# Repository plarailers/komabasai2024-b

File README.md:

# 第75回駒場祭（プランB）

開催日：2024年11月22日（金）～24日（日）

## 内容

【自動運転】
- train
  - 列車に書き込むコード
- master_controller
  - マスコンに書き込むコード
- wire_pole
  - 架線柱に書き込むコード
- point_switching
  - ポイントに書き込むコード
- ptcs
  - PC側の列車制御システム

【その他】
- experimental
  - 実験的なコードを置くところ
- rotary_encoder
  - ロータリーエンコーダの動作確認
- HiFreq_ADC
  - モータ電流ノイズを用いたIPSの実験

## インストール

```sh
git clone https://github.com/plarailers/komabasai2024-b.git
```

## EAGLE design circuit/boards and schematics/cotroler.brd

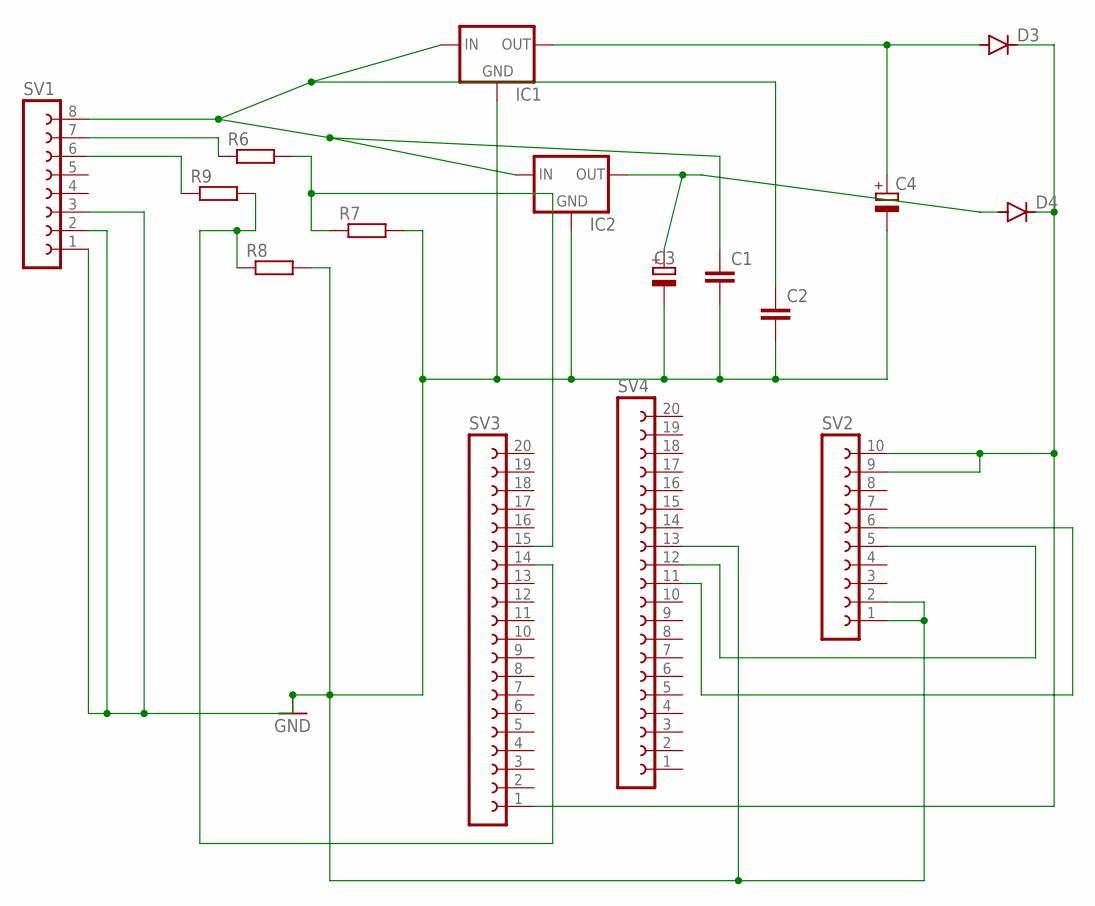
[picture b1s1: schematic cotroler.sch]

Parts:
C1, C2: C-EU025-024X044; C025-024X044
C3, C4: CPOL-EUE2.5-5; E2,5-5
D3, D4: DIODE-D-10; D-10
IC1, IC2: 78XXS
R6, R7, R8, R9: R-EU_0207/10; 0207/10
SV1: FE08-1; FE08
SV2: FE10-1; FE10
SV3, SV4: FE20-1; FE20

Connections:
GND: C1.2, C2.2, C3.-, C4.-, IC1.GND, IC2.GND, R7.2, R8.2, SV1.1, SV1.2, SV1.3, SV2.1, SV2.2, SV4.13
unnamed: R6.1, SV1.7
unnamed: SV2.5, SV4.12
unnamed: C1.1, C2.1, IC1.IN, IC2.IN, SV1.8
unnamed: R6.2, R7.1, SV3.15
unnamed: R9.1, SV1.6
unnamed: R8.1, R9.2, SV3.14
unnamed: C3.+, D4.A, IC2.OUT
unnamed: C4.+, D3.A, IC1.OUT
unnamed: SV2.6, SV4.11
unnamed: D3.C, D4.C, SV2.9, SV2.10, SV3.1

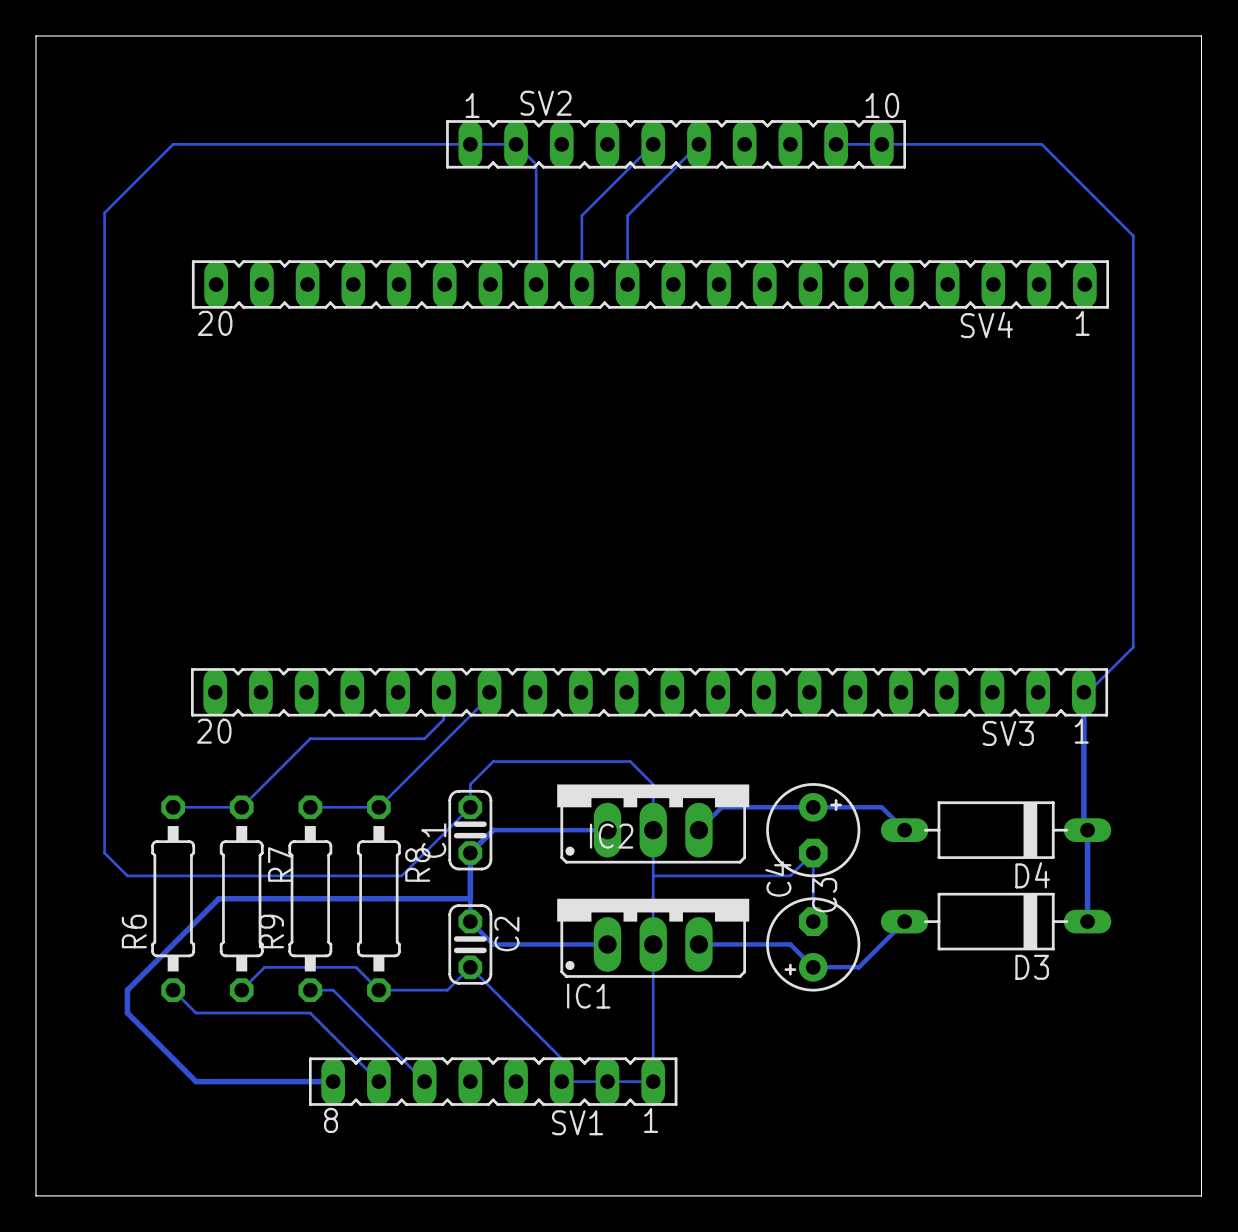
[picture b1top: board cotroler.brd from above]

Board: 2 copper layers, 64.8 x 64.4 mm, 16 parts (0 on the bottom side), 11 nets.

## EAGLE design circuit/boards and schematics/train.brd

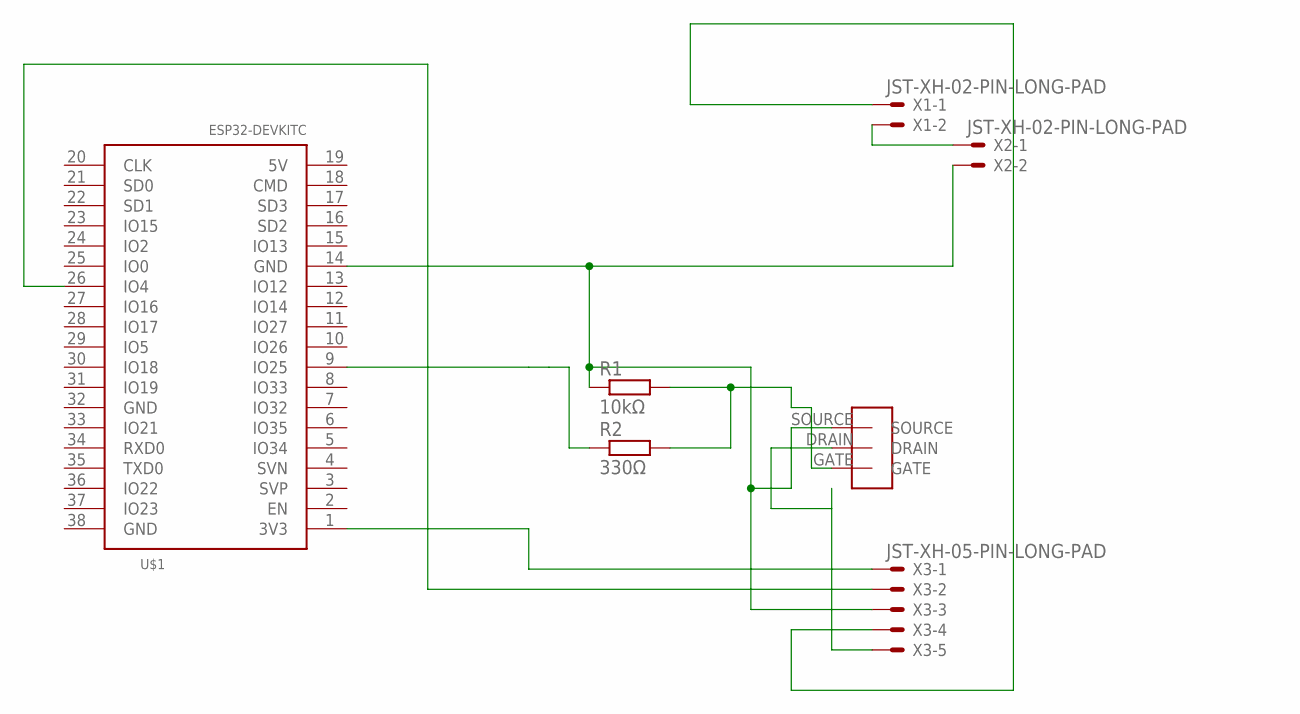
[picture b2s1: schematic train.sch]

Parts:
FET1: FET
R1: 10kΩ; 0207/10
R2: 330Ω; 0207/10
U$1: ESP32DEVKITC; ESP32-DEVKITC
X1, X2: JST-XH-02-PIN-LONG-PAD; JST-XH-02-PACKAGE-LONG-PAD
X3: JST-XH-05-PIN-LONG-PAD; JST-XH-05-PACKAGE-LONG-PAD

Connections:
unnamed: X1.1, X3.4
unnamed: FET1.SOURCE, R1.1, U$1.14 (GND), X2.2, X3.3
unnamed: FET1.GATE, R1.2, R2.2
unnamed: R2.1, U$1.9 (IO25)
unnamed: X1.2, X2.1
unnamed: U$1.1 (3V3), X3.1
unnamed: U$1.26 (IO4), X3.2
unnamed: FET1.DRAIN, X3.5

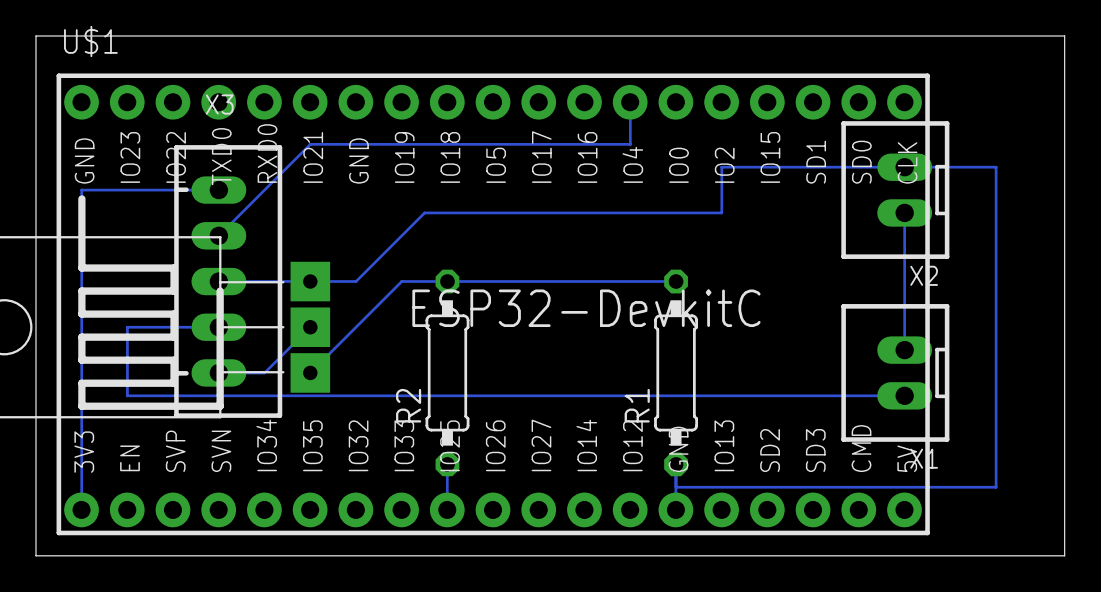
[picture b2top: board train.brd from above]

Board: 2 copper layers, 57.1 x 28.9 mm, 7 parts (0 on the bottom side), 8 nets.

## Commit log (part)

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2023-05-10 時計を自動で進める
2023-05-10 ロジックを修正
2023-05-10 待ち時間を可視化
2023-05-10 Commit from GitHub Actions (Build and commit ptcs_ui)
2023-05-10 Update test
    PCからの検証用コードを更新。サーボを4つ繋いだ時に安定して指令が送れることを確認。
2023-05-10 junction上に列車がいる場合は切り替えを禁止
2023-05-11 動作確認取れた
2023-05-11 ledcのサンプリングレートを更新
2023-05-11 フォトリフレクタと電流計の統合完了
2023-05-11 adcReadに名前変更
2023-05-11 calc_speedに停止目標の結果を反映
2023-05-11 非常発生ボタンの最終版です
2023-05-11 adcRead.hをtrain.inoに移動
2023-05-11 Add point switcher
2023-05-11 フォトリフクレクタ閾値調整
2023-05-11 Photo resetAll()を実装
2023-05-11 Fix server.py
    registerの引数の渡し方が間違っていたので修正
2023-05-11 レール長さを追加
2023-05-11 異常発生ボタンのつなぎこみ
2023-05-11 railway_configを更新
2023-05-11 IPS閾値をE5, E6, Dr(換装後)の3車両で動作確認済
2023-05-11 positionIDの場所を定義
2023-05-11 レール長の定義を移動 (一時的な策)
2023-05-11 Add Button
    異常発生ボタンと連携するためのクラスを定義
2023-05-11 Update server
    異常発生ボタンからのデータ受信用のコールバックを定義
2023-05-11 Update server
    異常発生ボタンをサーバーに組み込み
2023-05-11 Fix point_switcher
    registerの際の引数の撮り方の順番を変更
2023-05-11 Fix emergency button
    button->blocked
2023-05-11 button->blockec, ON/OFF時のサーボ角度変更
2023-05-11 Update Button
    receiveを追加
2023-05-11 すでにblockされたsectionに入っている列車は駅で止める
2023-05-11 Uターンレールを削除してレイアウト修正
2023-05-11 positionIDの検出を確実にした
2023-05-12 Update api
    ポイント切り替えのAPIにsendの処理を追加
2023-05-12 Update server
    動いてない
2023-05-12 線路長さをconstants.pyに集約
2023-05-12 列車初期位置の定義
2023-05-12 車両固有パラメータ
2023-05-12 fix t1 pos and import
2023-05-12 Fix server
    型エラー解消
2023-05-12 train_controller.pyでmotorRotationのテスト
2023-05-12 calc_direction, calc_stop, calc_speed を update に統合
2023-05-12 ブリッジ周りを整理
2023-05-12 inputを控えめにする
2023-05-12 ブリッジにセンサーと位置の対応を持たせる
2023-05-12 send と receive を整理
2023-05-12 ロギングレベルを INFO に設定
2023-05-12 速度指令をモーター入力に変換して送信
2023-05-12 横の navbar を削除 (邪魔なので)
2023-05-12 暫定版3_SerialBT不可
2023-05-12 列車に色を追加
2023-05-12 0.5 秒おきに列車とポイントに信号を送る
2023-05-12 ジャンクションの見た目を調整
2023-05-12 control.command を UI に表示
2023-05-12 センサー位置に向きの情報を持たせることで簡易的に APS を実装
2023-05-12 UI を 0.5 秒ごとに更新
2023-05-12 暫定版4_pID読み取り可
2023-05-12 👺を消した
2023-05-12 大文字小文字間違えてて草
2023-05-12 UI の表示座標を 路線図.drawio に合わせた
2023-05-12 受信キューをちゃんと消費するように修正
2023-05-12 Train::sendDataでflushを行い確実に送信する
2023-05-12 train_controller が ser のデコードを2回に1回しか行わない実装になっていたので修正
2023-05-12 基地局はTrainに接続できるまでconnectを繰り返す
2023-05-12 pyserialでポートOPENした際に基地局ESPがリセットする問題を修正
2023-05-12 flushに時間がかかった場合、基地局から切断されたと判断し停止する
2023-05-12 edit gitignore for arduino pre-compiled binary
2023-05-12 最新の基地局を反映
2023-05-12 変数・関数名を修正
2023-05-12 コンパイル通過
2023-05-12 フォトリフ閾値調整反映した
2023-05-12 Revert "受信キューをちゃんと消費するように修正"
    This reverts commit 8fd2208a3a1ff9fe2ebdff6878c580e2a1da7185.
2023-05-12 COM ポートスキャン用のコマンドを追加
2023-05-12 モーター入力値を整数にする (文字数の節約のため)
2023-05-12 とりあえず送信スレッドと受信スレッドを分離
2023-05-12 不要な while を削除
2023-05-12 一応 flush
2023-05-12 不要な while を削除、コードを整形
2023-05-12 コードを整形
2023-05-12 実測値をもとに delta_per_motor_rotation を設定
2023-05-12 停止目標の位置を調整 (センサーが中間車両 & 少し過ぎることを見越す)
2023-05-12 adcReadDoneでphotoPositionIDを更新
2023-05-12 stopに近づいていくときstop_distanceが変化しないのを修正
2023-05-12 photo_sensor1,2をsensorValue1,2に代入
2023-05-12 update を 0.1 秒ごとに呼ぶように固定
2023-05-12 lpf実装
2023-05-12 dtを1.0/ADC_SAMPLINGRATEに変更
2023-05-12 lpfコンパイル通ったわ
2023-05-12 位置を調整
2023-05-13 閾値調整
2023-05-13 edit gitignore
2023-05-13 flush廃止。基地局切断時はモータinputを0に
2023-05-13 五月祭 1 日目の調整
2023-05-13 Leaveを外すとうまくいきました
2023-05-13 五月祭 1 日目終了後の調整 (動作未確認)
2023-05-14 PutTrain ボタンを削除
2023-05-16 五月祭 2 日目の調整
2023-08-11 Add experimental/ble
2023-08-17 不要なコードの削除
2023-08-17 コンパイルを通した
2023-08-25 切断後に再度 advertising を始める
2023-08-25 独自の UUID を使う
2023-08-25 BLE アドレスを記載
2023-08-25 チップ ID と車両名を対応付けて表示
2023-09-03 poetry update
2023-09-03 dev dependencies を更新
2023-09-03 pyproject-flake8 → flake8 に変更
2023-09-03 line length の設定を統一
2023-09-03 PTCS 用に VS Code の設定を追加
2023-09-03 マルチルートワークスペースについて追記
2023-09-03 リント・フォーマットしてくれる君を追加
2023-09-03 自身の変更を追尾
2023-09-03 Commit from GitHub Actions (Lint and format ptcs)
2023-09-03 reviewdog を追加
2023-09-03 トリガーを pull_request に変更
2023-09-03 main ブランチを対象にする
2023-09-03 2>&1
2023-09-03 ステップを分離
2023-09-07 Poetry のインストール方法の説明に pip を使わない
2023-09-07 暫定版(動かない
2023-09-07 macOS 用に分岐
2023-09-07 動作確認済み
2023-09-07 E5,E6のmac用のアドレスを追加
2023-09-07 路線図を更新
2023-09-07 UI 上の junction と section を更新
2023-09-07 ジャンクション名を一時的に修正
2023-09-07 識別子の型名を `*Id` に統一
2023-09-08 Python の要求バージョンを 3.11 に更新
2023-09-08 section と junction をオブジェクト指向化
2023-09-08 train をオブジェクト指向化
2023-09-08 train の変更に合わせて ptcs_server を修正
2023-09-08 ロガーを追加
2023-09-08 内部時刻を Control に移動
2023-09-08 SensorPosition をオブジェクト指向化
2023-09-08 基底クラスで共通化
2023-09-08 Stop と Station をオブジェクト指向化
2023-09-08 railway_config, railway_state, railway_command を削除
2023-09-08 初期設定を別ファイルに移動
2023-09-08 列車と区間の一部メソッドを移動
2023-09-08 DirectPosition による Train と Stop の共通化
2023-09-08 列車とジャンクションの一部メソッドを移動
2023-09-08 PointDirection と JunctionConnection を移動
2023-09-15 列車の一部メソッドを移動
2023-09-15 README.md を追加
2023-09-15 説明に ATO と ATP を追加
2023-09-15 main 以外にプッシュしたときも CI を回す
2023-09-15 リロード対象を明示
2023-09-15 ptcs_server への引数を環境変数で渡す
2023-09-15 --debug オプションを追加
2023-09-15 ptcs_ui をウィンドウで開く
2023-09-15 デバッグ時に npm run dev を立ち上げ
2023-09-28 UI で一旦 API を使わない
2023-09-28 ロギングの強化
2023-09-28 fastapi と pydantic を更新
2023-09-28 main.pyで characteristicが1つしか読み込めない
2023-09-28 characteristic の指定を修正
2023-09-28 mac(intel)だとcharacteristicが1つしか読めない
2023-09-28 /state API の更新
2023-09-28 mac再起動したら通信できたわ
2023-09-28 ptcs_client を再生成
2023-09-28 ptcs_ui を新しい API に合わせる
2023-09-28 レールの接続の仕方を更新
2023-09-28 usb_bt_bridge を ptcs_bridge に改名
2023-09-28 train.inoをbleに変更した
2023-09-28 エンコーダを追加
2023-09-28 bleの機能を必要なものに限定
2023-09-28 PWMの部分を修正
2023-09-29 列車との通信のシミュレーターを追加
2023-09-29 列車と実際に通信を行うクライアントを追加
2023-09-29 TrainSimulator と TrainClient の共通化
2023-10-02 コードの構成を修正
2023-10-02 fix: エンコーダ割込が繰り返し起きる問題、std::stoiがコンパイルできない問題を修正
2023-10-02 コメントを追加
2023-10-02 電源電圧をnotifyするように変更
2023-10-07 Bridge2 を追加
2023-10-07 レイアウトの長さを調節
2023-10-07 verification の追加
2023-10-07 列車の長さをパラメータ化
2023-10-07 列車の末尾を表示
2023-10-07 一旦 _calc_direction を無効にし、ジャンクションを手動で切り替えられるようにする
2023-10-07 列車の先頭から末尾までの全体を経路上に表示
2023-10-07 デザインを調整
2023-10-08 障害物オブジェクトを追加
2023-10-08 列車を5台に増やす
2023-10-08 railwayState と railwayUI の共通要素を描画
2023-10-08 bridge の方も列車を5台に増やす
2023-10-08 Obstacle.position を UndirectedPosition として一般化
2023-10-08 停止位置の探索を一般化
2023-10-08 ジャンクションに手動で設定した方向を持たせる
2023-10-08 障害物の発生を画面から切り替えられるようにする
2023-10-08 障害物が発生した区間の手前のポイントを切り替える
2023-10-08 マスコンのコードが出来ました
2023-10-08 合流点のポイントを最も近い列車のいる方に切り替える
2023-10-11 構成図の更新
2023-10-11 分岐点の向きは決め打ち
2023-10-11 Juntion.find_nearest_train をメソッド化
2023-10-11 古い _calc_direction を削除
2023-10-11 各列車の速度を表示
2023-10-11 BLEアドレスを追加
2023-10-11 路線図に駅を配置
2023-10-11 停止目標を設置
2023-10-11 add gitignore on train for Arduino extensinos
2023-10-11 fix: train_controller の電圧のバイトオーダーはリトル。ESPは基本リトルらしい
2023-10-12 bleを入れると動かない
2023-10-12 架線柱との通信を確認
2023-10-12 fix: 回転数notify処理を割り込みではなくloopに変更
2023-10-12 ちゃんと架線柱倒れます
2023-10-12 TrainClient に対しては速度ではなくモーター入力を送る
2023-10-12 古い bridge のコードを削除
2023-10-12 関数を整理
2023-10-12 mft2023 用の bridge の設定を分離
2023-10-12 終了処理を修正
2023-10-12 アドレスを追加
2023-10-13 T2~T4を追加
2023-10-13 add: controlとserverにvoltage_mVを追加
2023-10-13 add: uiに電圧を追加
2023-10-13 サーボの角度を調整
2023-10-13 APS を設置、実機で確認
2023-10-13 駅を一旦除いて安定性を確認
2023-10-13 voltage を統合
2023-10-13 通信切れた時にモータ停止
2023-10-13 BLE通信部分が完成しました
2023-10-13 マスコンを統合
2023-10-13 終了時、未接続の列車に速度ゼロを送ろうとしない
2023-10-13 BLE write 時にレスポンスを求めない（時間がかかり、内部の時計が進まなくなるため）
2023-10-13 衝突を避けるための探索に各列車先頭の位置も含める
2023-10-13 旧来の Bluetooth による列車や異常発生ボタンとの接続を削除
2023-10-13 パラメータ調整して実機で動作確認
2023-10-13 センサーを追加、架線柱をつけて動作確認
2023-10-14 列車の色を現実と合わせた
2023-10-14 MFT 1日目終了時のコード
2023-10-15 2日目13:30時点のコード: 架線柱退避時時ポイント変更のバグあり
2023-10-15 hotfix: 合流点の切り替えの探索区間をひとつ伸ばす
2023-10-28 使われていない車載コードを削除
2023-10-28 使われていない自動運転システムを削除
2023-10-28 使われていない回路のデータを削除
2023-11-05 uidを10桁に変更
2023-11-23 positionIDを10バイトに変更
2023-11-23 ポイントをBLE化
2023-11-23 制御と通信のループを分離
2023-11-23 角度を調整した
2023-11-23 PTCS に PointClient を追加
2023-11-23 point1の角度を調整
2023-11-23 古い PointSwitcher を削除
2023-11-23 依存から pyserial を削除
2023-11-23 point_switching_archive を削除
2023-11-23 ハンドルで速度を指定するように変更
2023-11-23 UIDのサイズを4or7バイトにした
2023-11-23 APS の位置 ID を 4, 7, 10 バイトいずれかの MIFARE PICC UID に変更
2023-11-23 停止点の位置を調整
2023-11-23 [WIP] 駅停止アルゴリズムを改善
2023-11-23 [WIP] 各 ESP32 との通信を独立のループで行う
2023-11-24 実機で動作確認して調整
2023-11-24 POINT0 の MAC アドレスを修正
2023-11-24 wirepoleとmastercontrollerのUUIDを追加
2023-11-24 駒場祭1日目終了時点でのコード
2023-11-25 駒場祭2日目終了時点でのコード(変更はパラチュンのみ)
2023-11-26 手動操縦のとき ATO を解除
2023-11-26 起動時に架線柱の状態を読み取る
2023-11-26 駒場祭3日目終了時点でのコード
2023-11-29 接続部分の古いコードを削除
2023-11-29 古い _calc_stop を削除
2024-05-05 gogatsusai2024 の路線図を追加
2024-05-11 頂点と辺の接続に基づく路線図抽出スクリプトを追加
2024-05-11 UI の定義を移動
2024-05-11 路線図データを更新
2024-05-11 抽出したデータを出力
2024-05-11 結果を ID 順にソート
2024-05-11 settings.json を更新
2024-05-11 路線の定義を自動生成
2024-05-12 路線図 v3 を作成
2024-05-12 閉塞区間を踏まえて路線図 v3 を編集
2024-05-12 control と ui に路線図 v3 を適用
2024-05-12 見た目を調整
2024-05-13 閉塞区間を割り振り
2024-05-13 システムを固定閉塞システムと移動閉塞システムに分割
2024-05-13 とりあえず移動閉塞と同じように動かす
2024-05-15 列車のセクション変化などのイベント通知機構を導入
2024-05-15 (WIP) ポイント切り替えアルゴリズムを記述
2024-05-16 センサー位置を設定
2024-05-16 列車の長さを調整
2024-05-16 自動生成するセクションの長さを調整
2024-05-17 列車の駅停止判断を記述
2024-05-17 ファイル名を変更（gogatsusai2024.py → gogatsusai2024_generated.py）
2024-05-17 ファイル名を変更（config.py → gogatsusai2024.py）
2024-05-17 車両とポイントを設定（対応は未定）
2024-05-17 アドレスを追加．通信を確認した
2024-05-17 3台まで動いた．ポイントが動かないが
2024-05-17 閉塞を計算する
2024-05-17 ジャンクション j12, j14 を廃止
2024-05-18 ブリッジの設定に対応するコンポーネントが存在しないときに警告
2024-05-18 合流点の 2 つ前のセクション終端で止まる不具合を修正
2024-05-18 駅停止をもっと急にする
2024-05-18 _calc_direction がエラーで止まっていたのを修正
2024-05-18 プロパティを修正（train.mileage → train.head_position.mileage）
2024-05-18 CI が失敗するのを修正
2024-05-18 1日目終了
2024-05-18 路線図 v5 に更新
2024-05-19 2日目朝安定動作版
2024-05-19 駅停止機能を省く
2024-05-19 2日目最終版
2024-11-10 (WIP) komabasai2024 テスト用レイアウトを追加
2024-11-10 列車の種別を UI 上に表示
2024-11-10 列車の種別とポイントの動きを記述
2024-11-10 経堂だけ3両成功ver
2024-11-10 5両編成(衝突バグあり)
2024-11-16 change: pyproject.tomlのpythonバーション指定を変更
2024-11-16 add: poetryが無くても実行できるようにrequirements.txtを追加
2024-11-16 fix: T0のアドレス間違いを修正
2024-11-16 fix: PTCS終了時に列車の非同期タスクをキャンセルする処理を追加
2024-11-17 chore: poetry install でコケるため Python のバージョンを指定
2024-11-17 chore: 依存関係をアップデート
2024-11-17 chore: npm audit fix
2024-11-17 feat: 同じ閉塞 ID でもポイントの状態に応じて区切り方を変える
2024-11-17 fix(ui): t5 の色を修正
2024-11-17 feat: 次のセクションのポイントが開通していなかったら止まる
2024-11-17 fix: ポイントを見る先を閉塞区間が変わる次のセクションまで伸ばす（切り替え禁止の判定が何かおかしい）
2024-11-17 fix: デフォルトのポート番号を 5000 ではなく 8000 にする
2024-11-17 feat: FastAPI の終了時の処理を lifespan で指定する
2024-11-17 chore: 非推奨の logger.warn を logger.warning に変更
2024-11-18 ci: Python と Poetry を更新
2024-11-18 ci: Node.js を更新
2024-11-18 ci: 自身の変更を追尾
2024-11-18 feat(ui): 列車の色を種別に合わせて表示
2024-11-18 feat(ui): 列車の ID を表示
2024-11-18 feat(control): ポイントに要求キューを持たせ、列車の要求順を遵守する（現地未検証）
2024-11-19 fix: タスクのエラーハンドリングをちゃんとやる
2024-11-19 feat: ログに時刻を表示
2024-11-20 fix: ポイントが自分の方に向いていないときの判定を修正
2024-11-20 fix: 駅停車中はキューに入れないようにする
2024-11-20 feat!: 経堂駅前で合流する路線図 test_v2 に更新
2024-11-20 fix: ポイント ID の変更忘れを修正
2024-11-21 train_controllerにテスト用コードを追加
2024-11-21 feat!: 取り急ぎ本番用路線図 v1 を追加
2024-11-21 マスコンのテストコード作成
2024-11-21 feat: 快速急行を実装
2024-11-21 feat: 接続をリトライ
2024-11-21 feat: 列車がすべて接続されるまで待つ（現地確認済み）
2024-11-21 feat: 駅で停車する前の閉塞区間で減速する（現地確認済み）
2024-11-21 fix: 表の配置を改善
2024-11-21 feat!: マスコンを復活
2024-11-21 feat!: 手動操縦車を車庫に入れる路線図 v2 に変更
2024-11-23 fix: Ctrl+C が効かない・サーバーが始まらない問題を修正
2024-11-23 feat: ポイントも待機対象に入れる
2024-11-23 fix: 接続されていないなら disconnected と言わない
2024-11-23 feat: いずれかのタスクでエラーが出たときに接続を正常終了させる
2024-11-23 fix: ポイントが自分の方に向くように要求する範囲を修正
2024-11-24 車庫運用(現地確認済み)
2024-11-24 feature: 手動運転用の種別(LocalManual)を実装
2024-11-24 fix: T7の種別変更忘れを修正
2024-11-24 fix: コミット忘れを修正
2024-11-24 ロマンスカーを運転体験用に変更
2024-11-24 fix: 車庫に入った列車が出口の合流点を占有してしまう問題を修正
2024-11-24 fix(ci): data ディレクトリを ptcs-ui-build の追跡対象に含める
